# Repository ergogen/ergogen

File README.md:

# Ergogen

***Ergonomic Keyboard Generator***

<br>

The project aims to provide a common configuration format to describe ***ergonomic*** 2D layouts and generate automatic plates, cases, as well as un-routed PCBs for them. The project grew out of (and is an integral part of) the [Absolem keyboard], and shares its [Discord] server as well.

<div align = center>
<br>
<br>
<br>

---

[![Button WebUI]][WebUI]
[![Button Documentation]][Documentation]
[![Button Discord]][Discord]
[![Button Donate]][Donate]

---

</div>

<br>
<br>

## Getting Started

Until there's a proper "Getting started" guide, try getting acquainted with **Ergogen** by following these steps in order:

<br>

1. Read the **[Documentation]**.
    
    D'uuh.
    They're not complete by any measure, but should give you a fairly good idea what you're dealing with here.

    <br>
    
2. Try one of the web-based deployments.

    [![Button Official]][WebUI]   
    [![Button Unofficial]][Unofficial]
   
    (The difference being that Stable runs the latest official release, while Nightly offers early access to in-progress features, both for the Ergogen engine and the UI.)
    
    Load example configs, click things, rewrite things, look at outputs and see if things start to make sense.
   
    There is no need for you to download the **CLI** unless you want to do one of the following:
   
    - Preview in-development features
    - Use custom modifications
    - Contribute code
   
    <br>

3. Search the [`ergogen`][Topic] topic on GitHub.

    There, you can look at (and reverse engineer) a variety of real life configs using **Ergogen**.
    Pop them into the web UI to see what they do, tinker with them and things should start to make more sense.

    <br>

4. If a question persists after all of the above, feel free to ask it over on **[Discord]** and we'll do our best to help you out.

<br>

## Contributions

Feature ideas, documentation improvements, examples, tests, or pull requests welcome!
Get in touch on our **[Discord]**, and we can definitely find something you can help with, if you'd like to.

From an administrative standpoint, please note that we'd like to keep the Git history linear and the test suite comprehensive, so if you do issue a PR, make sure it's A) a straight chain of commits, B) it's always rebased on the current `develop`, and C) the test coverage remains at 100%.

<br>

## Sponsors

Huge thanks go to everyone who chooses to support my work!
But even huger thanks are due to the following, *distinguished* sponsors:

- [perce](https://madebyperce.com/)
- [Cache](https://github.com/MvEerd)
- [Neil Gilmour](https://github.com/neilgilmour)
- [ochief](https://github.com/ochief)
- [Alyx Brett](https://github.com/alyx-brett)

<!----------------------------------------------------------------------------->

[Absolem keyboard]: https://zealot.hu/absolem
[Documentation]: https://docs.ergogen.xyz
[Discord]: http://discord.ergogen.xyz
[WebUI]: https://ergogen.xyz
[Unofficial]: https://ergogen.ceoloide.com/
[Topic]: https://github.com/topics/ergogen
[Donate]: https://github.com/sponsors/mrzealot

<!--------------------------------{ Buttons }---------------------------------->

[Button WebUI]: https://img.shields.io/badge/Deployment-37a779?style=for-the-badge&logoColor=white&logo=AppleArcade
[Button Official]: https://img.shields.io/badge/Stable-37a779?style=for-the-badge
[Button Unofficial]: https://img.shields.io/badge/Nightly-yellow?style=for-the-badge
[Button Documentation]: https://img.shields.io/badge/Documentation-1793D1?style=for-the-badge&logoColor=white&logo=GitBook
[Button Discord]: https://img.shields.io/badge/Discord-5865F2?style=for-the-badge&logoColor=white&logo=Discord
[Button Donate]: https://img.shields.io/badge/Donate-EA4AAA?style=for-the-badge&logoColor=white&logo=githubsponsors

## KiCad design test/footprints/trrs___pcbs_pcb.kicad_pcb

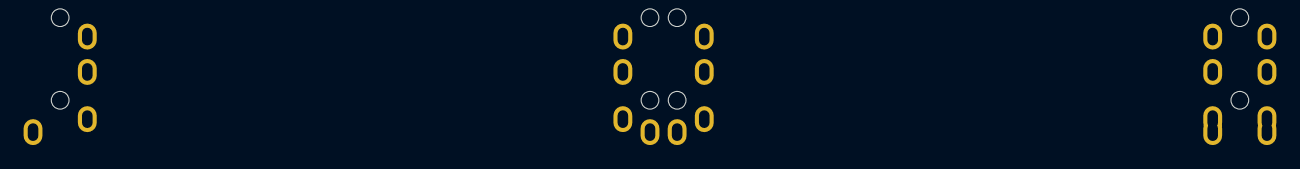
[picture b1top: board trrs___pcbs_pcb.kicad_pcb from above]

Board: 2 copper layers, 3 parts (0 on the bottom side), 4 nets, no tracks yet.

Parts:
TRRS1, TRRS2, TRRS3: TRRS-PJ-320A-dual

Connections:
A: TRRS1.1, TRRS2.1, TRRS3.1
B: TRRS1.2, TRRS2.2, TRRS3.2
C: TRRS1.3, TRRS2.3, TRRS3.3
D: TRRS1.4, TRRS2.4, TRRS3.4

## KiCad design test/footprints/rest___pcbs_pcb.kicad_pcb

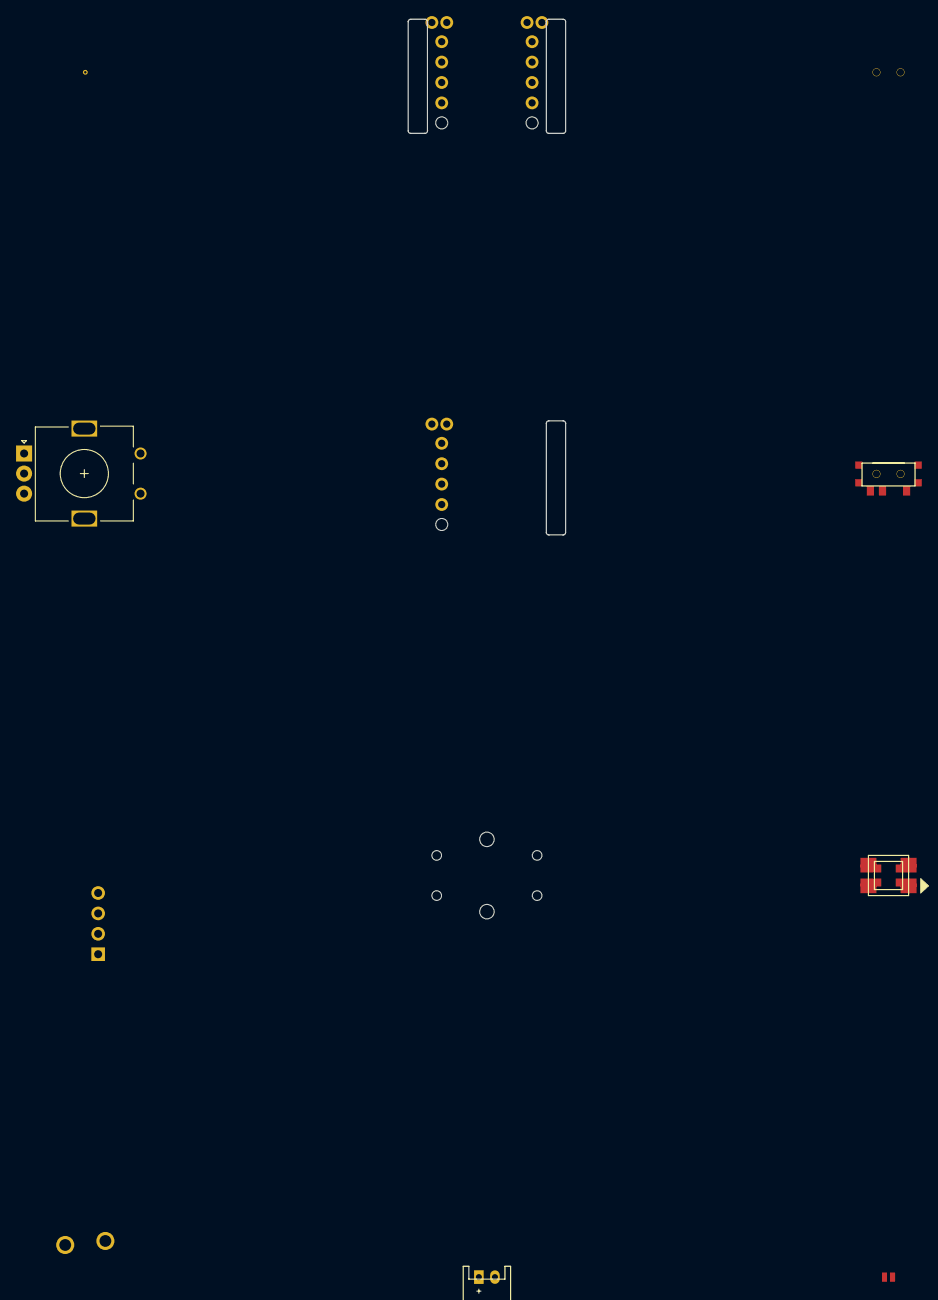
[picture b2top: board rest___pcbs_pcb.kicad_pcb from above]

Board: 2 copper layers, 9 parts (0 on the bottom side), 6 nets, no tracks yet.

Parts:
J1: Jumper
JST1: JST_PH_S2B-PH-K_02x2.00mm_Angled
LED1: WS2812B
OLED1: OLED; OLED_headers
ROT1: rotary_encoder
S1: ALPS
S2: OMRON_B3F-4055
T1, T2: SPDT_C128955

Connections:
GND: LED1.3, LED1.33, OLED1.1
VCC: LED1.1, LED1.11, OLED1.2
din: LED1.4, LED1.44
dout: LED1.2, LED1.22
from: J1.1, ROT1.1, S1.1, S2.1, S2.2, T1.1, T2.1
to: J1.2, ROT1.2, S1.2, S2.3, S2.4, T1.2, T2.2

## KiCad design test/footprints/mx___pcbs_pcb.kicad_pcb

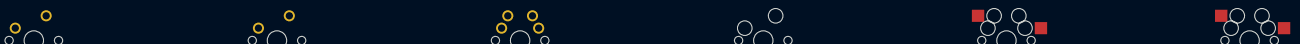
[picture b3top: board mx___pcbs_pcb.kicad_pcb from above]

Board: 2 copper layers, 6 parts (0 on the bottom side), 2 nets, no tracks yet.

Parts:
S1, S2, S3, S4, S5, S6: MX

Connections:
from: S1.1, S2.1, S3.1, S4.1, S5.1, S6.1
to: S1.2, S2.2, S3.2, S4.2, S5.2, S6.2

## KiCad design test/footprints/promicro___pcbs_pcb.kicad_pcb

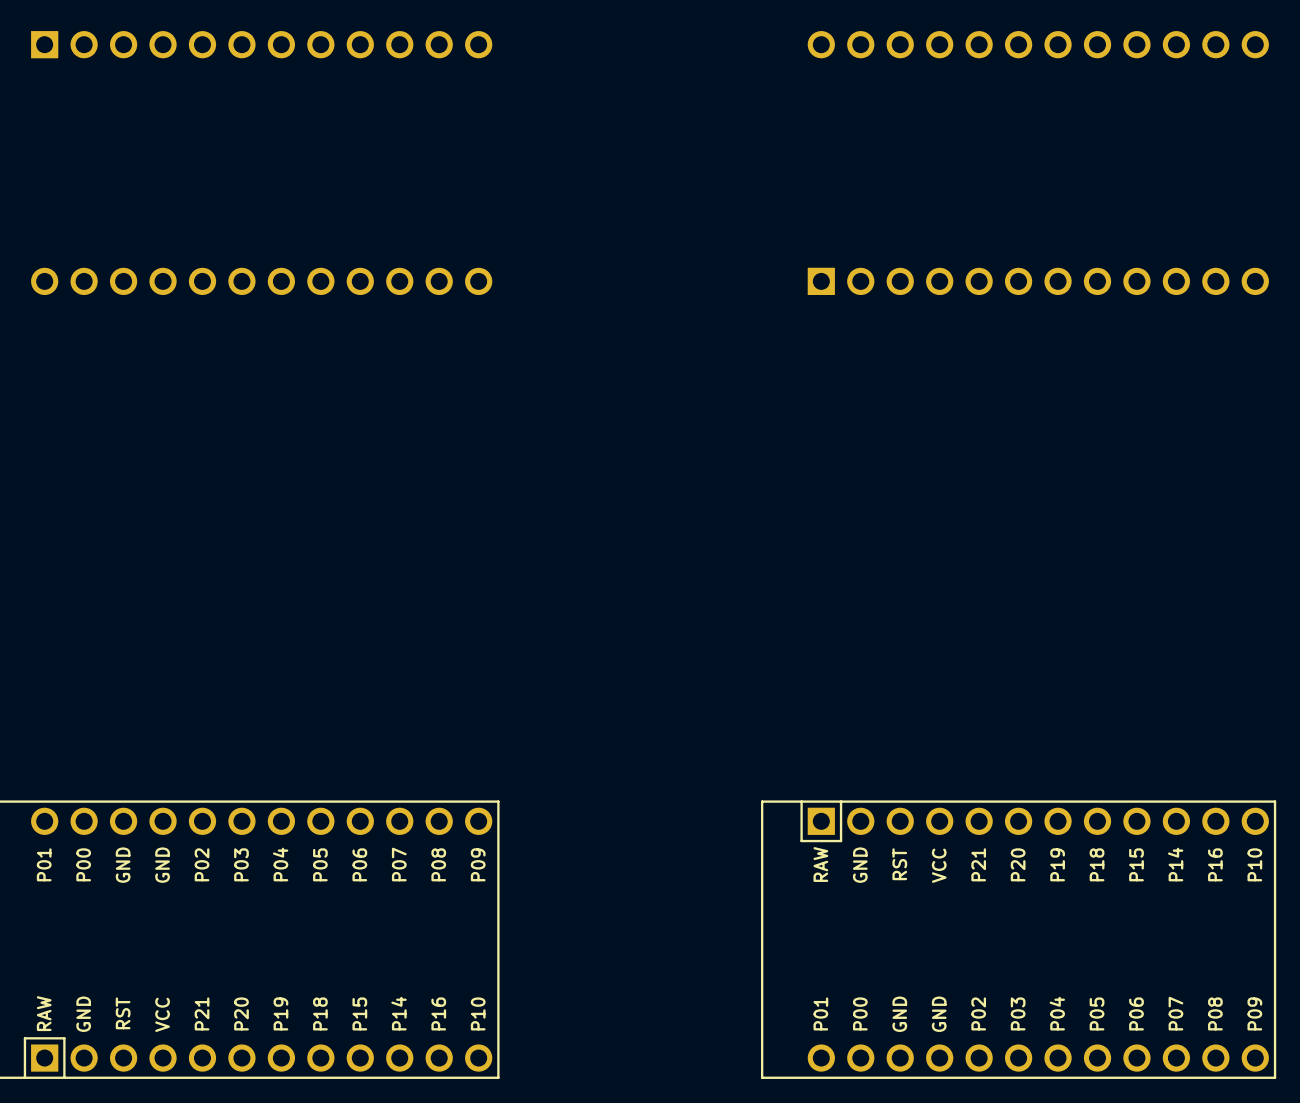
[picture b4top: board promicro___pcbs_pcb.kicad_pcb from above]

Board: 2 copper layers, 4 parts (0 on the bottom side), 22 nets, no tracks yet.

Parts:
MCU1, MCU2, MCU3, MCU4: ProMicro

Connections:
GND: MCU1.2, MCU1.15, MCU1.16, MCU2.2, MCU2.15, MCU2.16, MCU3.2, MCU3.15, MCU3.16, MCU4.2, MCU4.15, MCU4.16
P0: MCU1.14, MCU2.14, MCU3.14, MCU4.14
P1: MCU1.13, MCU2.13, MCU3.13, MCU4.13
P2: MCU1.17, MCU2.17, MCU3.17, MCU4.17
P3: MCU1.18, MCU2.18, MCU3.18, MCU4.18
P4: MCU1.19, MCU2.19, MCU3.19, MCU4.19
P5: MCU1.20, MCU2.20, MCU3.20, MCU4.20
P6: MCU1.21, MCU2.21, MCU3.21, MCU4.21
P7: MCU1.22, MCU2.22, MCU3.22, MCU4.22
P8: MCU1.23, MCU2.23, MCU3.23, MCU4.23
P9: MCU1.24, MCU2.24, MCU3.24, MCU4.24
P10: MCU1.12, MCU2.12, MCU3.12, MCU4.12
P14: MCU1.10, MCU2.10, MCU3.10, MCU4.10
P15: MCU1.9, MCU2.9, MCU3.9, MCU4.9
P16: MCU1.11, MCU2.11, MCU3.11, MCU4.11
P18: MCU1.8, MCU2.8, MCU3.8, MCU4.8
P19: MCU1.7, MCU2.7, MCU3.7, MCU4.7
P20: MCU1.6, MCU2.6, MCU3.6, MCU4.6
P21: MCU1.5, MCU2.5, MCU3.5, MCU4.5
RAW: MCU1.1, MCU2.1, MCU3.1, MCU4.1
RST: MCU1.3, MCU2.3, MCU3.3, MCU4.3
VCC: MCU1.4, MCU2.4, MCU3.4, MCU4.4

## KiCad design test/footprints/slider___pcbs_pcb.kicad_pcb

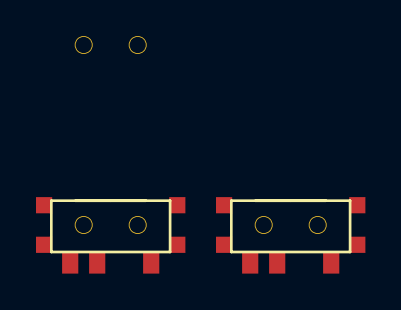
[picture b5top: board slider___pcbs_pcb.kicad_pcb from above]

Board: 2 copper layers, 3 parts (0 on the bottom side), 2 nets, no tracks yet.

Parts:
T1, T2, T3: SPDT_C128955

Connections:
A: T1.1, T3.1
COM: T1.2, T2.2, T3.2

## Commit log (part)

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2022-01-11 Outlines rewrite theoretically done
2022-01-12 (fix) allow mirroring around origin
2022-01-15 Filter implementation started
2022-01-15 Outlines rewrite, part 2
2022-01-15 Add filter tests
2022-01-16 Outlines rewrite actually done
2022-01-18 Roadmap update
2022-01-20 Bump patch version
2022-01-22 Support string templating for key-level attributes
2022-01-23 Fix rollup build warning
2022-01-23 More flexible semver handling
2022-01-24 Improve readme
2022-02-27 Support orient/rotate towards other points
2022-02-27 Make reference dumping easier during testing
2022-02-27 Changelog started
2022-03-26 Bump minimist from 1.2.5 to 1.2.6
    Bumps [minimist](https://github.com/substack/minimist) from 1.2.5 to 1.2.6.
    - [Release notes](https://github.com/substack/minimist/releases)
    - [Commits](https://github.com/substack/minimist/compare/1.2.5...1.2.6)
    ---
    updated-dependencies:
    - dependency-name: minimist
2022-03-26 fix: Remove superfluous rotation of 180 on a rectangular pad
2022-04-12 Update ergogami.yaml
    Clear and orginize
2022-04-12 Update ergogami.yaml
    wiring route fix
2022-04-12 Update ergogami.yaml
    fix wiring
2022-04-16 3D de-standalone-ification
2022-04-16 Outline scaling
2022-05-02 TRRS: properly showing p.ref instead of 'REF**'
2022-05-09 udpate promicro pretty
2022-05-09 samples
2022-05-17 Rename ergogami_alpha.yaml to Ergogami/ergogami_alpha.yaml
2022-05-18 More consistent formatting for promicro footprint + tests
2022-05-22 fixes
2022-05-22 ergogami v2 init
2022-05-22 update ergogami v2 alpha
2022-05-29 Outlining improvements
2022-05-31 Adjusted README Name
2022-05-31 Added License Badge
2022-05-31 Moved Getting Started Into Dedicated File
2022-05-31 Added Quicklinks
2022-05-31 Formatted Description + Added Showcase
2022-05-31 Adjusted Spacing
2022-08-08 Prevent duplicate net names between the main board and its mirror
2022-08-25 connects pads and THT terminals for less routing
2022-11-09 FULL
2022-11-14 Footprint sideloading tests
2022-11-22 Filtering applied to PCBs as well
2022-12-03 Generalize `asym` usage
2022-12-03 Minor comment fixes
2022-12-03 Improve PCB test readability
2022-12-03 Fix diode THT pad order
2022-12-04 Make outline/pcb anchor adjustments more generic
2022-12-04 Extend footprint test coverage
2022-12-04 Footprint parameter flattening, round 1
2022-12-04 Per-footprint mirror overrides, better coordinate support
2022-12-18 Missing const for web deployment
2022-12-18 Link updates
2023-01-08 Bump json5 from 2.2.1 to 2.2.3
    Bumps [json5](https://github.com/json5/json5) from 2.2.1 to 2.2.3.
    - [Release notes](https://github.com/json5/json5/releases)
    - [Changelog](https://github.com/json5/json5/blob/main/CHANGELOG.md)
    - [Commits](https://github.com/json5/json5/compare/v2.2.1...v2.2.3)
    ---
    updated-dependencies:
2023-01-11 fix: typo in error message if using incorrect type for stagger
2023-01-14 ignore line endings in cli tests
2023-01-14 expand code coverage for `choc` footprint
2023-01-14 expand code coverage for `mx` footprint
2023-01-14 expand code coverage for `pad` footprint
2023-01-14 expand code coverage for `anchor.js`
2023-01-14 New Kicad format plus tests
2023-01-14 expand code coverage for `filter.js`
2023-01-14 fix: use all but last character as `expand` value in `expand_shorthand`
2023-01-15 expand code coverage for `pcbs.js`
2023-01-15 expand code coverage for `kle.js`
2023-01-16 Add parenthesis to title block
2023-01-23 Bugfix for `expand_shorthand` (#79)
2023-01-23 Improve readme formatting (#62)
    * Fixed LICENSE File Name
    * Adjusted README Name
    * Formatted Contribution Section
    * Added License Badge
    * Formatted Getting Started
    * Moved Getting Started Into Dedicated File
2023-01-23 Fix multiple extrusions of the same outline in cases
2023-01-23 Readme postprocessing
2023-01-23 test: code coverage for `expand_shorthand`
2023-01-23 Add array to footprint param types (#76)
2023-01-23 Getting coverage to 100%
2023-01-31 fix: handle backslashes in windows tests
2023-02-09 Filter/mirror bugfix
2023-03-17 Templating bugfix (#86)
2023-03-17 4.0.1
2023-03-17 v4.0.1 release as WebUI 1.4.1
2023-03-18 Filter negation bugfix
2023-03-18 v4.0.2 release as WebUI 1.4.2
2023-03-29 Add extra note on "read documentation" about v4
2023-04-19 Add pro micro pretty footprint
2023-04-19 create fourne w correct footprints
2023-05-01 Add donate button to readme
2023-05-08 Sponsor fixes
2023-05-20 Independent per-point adjustment
2023-05-20 4.0.4
2023-05-20 v4.0.4 release as WebUI 1.4.3
2023-05-31 Allow outline adjusts to use shape-specific units
2023-06-17 add outline to niceview
2023-07-15 Added intersect aggregator
2023-07-17 Addressed stylistic PR feedback
2023-07-17 Revert "Set the rotation of the intersected point to the second point’s rotation"
    This reverts commit d210a98f79a8866519fc9695487a9ea235167b8b.
2023-07-18 Add assert to check for exactly 2 parts
2023-07-19 Change the assert string to use ${name.length}
2023-07-19 Update intersect logic to consider negative Y axis
2023-07-19 Add intersect aggregator (#102)
    * Added intersect aggregator
    * Addressed stylistic PR feedback
    * Set the rotation of the intersected point to the second point’s rotation
    * Revert "Set the rotation of the intersected point to the second point’s rotation"
    This reverts commit d210a98f79a8866519fc9695487a9ea235167b8b.
    * Adjusted aggregate function to not need axis1 and axis2 parameters
2023-08-13 feat: add parametric breakout board
2023-08-24 Add point as a parameter to footprints
2023-09-09 add 'global_net' to params structure for access (read and read/write) to global nets in footprints
2023-09-18 Adding option for circle radius to be an anchor.
    Rather than just accepting a number, the circle outline can now also
    accept an anchor. When an anchor is given, the radius is calculated as
    the distance from the origin of the circle(s) to the anchor point.
2023-09-18 Adding midpoint aggregator.
    The midpoint aggregator takes 3 points and finds a "midpoint" that is
    equidistant to all the given points.
2023-12-25 Inject outlines from SVGs in bundle
2023-12-25 Add jsdom dependency (oops)
2023-12-25 Fix tests and add coverage for injected outlines
2023-12-28 Change test references from src/ to build/ and update more configs
2023-12-28 Convert point.js to point.ts
2024-01-01 Add type declarations for node dependencies
2024-01-01 add trackball footprint file
2024-01-01 get rotation right
2024-01-04 Allows more than one via
    The .kicad_pcb file seems to be invalid if you have two vias with a REF** reference
    This change puts in a dynamic reference and defaults the designator to V
2024-01-22 Package audit
2024-01-23 Injectable PCB templates
2024-03-29 Outsource kicad outline conversion to pcb templates
2024-04-09 KiCad8 PCB template
2024-04-09 Template dependency injection
2024-04-14 Prevent circular dependencies in $extends
2024-05-12 when --clean enabled instead of deleting output dir just clean up its content
2025-08-23 Remove `bezier` outline code
2025-11-01 MakerJS dependency reset and tests
2025-11-01 Add skeleton for closed Bezier splines
2025-11-01 Fix variable declaration
2025-11-01 Add check for number of points based on type, and default to `quadratic` type
2025-11-01 Fix wrong variable declaration
2025-11-01 Add bezier utility function
2025-11-01 Remove wrong `bezier` package dependency
2025-11-01 Add `hull` type to outlines
2025-11-01 Fix bounding box logic and BezierCurve creation
2025-11-01 Remove require for Bezier
2025-11-01 Add intermediate points
2025-11-01 Add rotation test case
2025-11-01 Switch from `let` to `const` since variables are not modified
2025-11-01 Add parameter / syntax validation
2025-11-01 Fix rollup.config.mjs (use Node 20+ import syntax)
2025-11-01 Change the path segment logic so that the starting point is taken from the previous segment
2025-11-01 Fix: Resolve variables in mirror properties
    Previously, when a variable was used for a property inside a `mirror`
    configuration (e.g., `width: my_var`), it was not resolved correctly.
    This was because the sanitization and variable resolution process was
    not re-applied after the mirrored point's metadata was extended with
    the mirror configuration.
    This commit fixes the issue by passing the `units` object to the
2025-11-01 `--clean` now cleans the output dir instead of deleting it
    The most common behavior for a CLI `--clean` flag is to delete just the contents of the artifact / output folder, not the folder itself.
    This ensures that the folder (and especially any required permissions or configuration) remains in place for subsequent runs, avoiding issues where the folder needs to be recreated.
    Deleting only the contents is safer and more user-friendly, especially if other processes or scripts expect the folder to exist.
    This commit closes https://github.com/ergogen/ergogen/pull/131
2025-11-01 Address `npm audit` vulnerabilities with `npm audit fix`
2025-11-01 Update npm packages to their latest version
    Additionally, changed `yaml.safeLoad` to `yaml.load` as this is now safe by default in js-yaml 4.
    This commit closes https://github.com/ergogen/ergogen/pull/149
2025-11-01 Add `height` to the `mirror_variable` test (issue #145)
    Test coverage highlighted that only `width` but not `height` was explicitly being tested. Slightly amended the test to add `height` as well, to reach 100% test coverage.
2025-11-01 Add test cases for `path`
    Test cases cover both cases when one of the segment types is used first, meaning it defines all points, or when it's defined `[2nd...N-th]` in the path, meaning the first point is inherited from the 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
2025-11-01 Remove redundant `operation: stack` entries from path outlines
2025-11-01 fix(test): use portable command for checking file permissions
2025-11-01 Implement date mocking, to ensure `kicad8` tests are deterministic
    The `kicad8.js` template generates `*.kicad_pcb` outputs that contain a dynamic date, based on global `Date` object. This makes tests fail since they compare to a fixed output reference, with an stat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
2025-11-01 Add additional `line` segment to path definition to reach 100% coverage for `outlines.js`
2025-11-01 Remove unused `bezier` code, and fix `s_curve` switch case
2025-11-01 refactor(clean): remove `clean` CLI test command and related output files
    The command used is tied too much to *nix environments and doesn't work fully across different OS.
    While coverage remains at 100%, a different test will be created for the `--clean` argument
2025-11-02 Support for newer OpenJSCAD
2025-11-02 Update README to remove comment about official GUI
2025-11-02 4.2.1
2025-11-09 Update generator version to 4.2.1 in KiCad PCB template
2025-11-09 Add clockwise and counter-clockwise options to hull configuration and update related DXF files
2026-01-28 Add 'maxArcFacet' meta field to fix issue where all circles & arcs have exactly 32 segments
2026-05-12 Add CadQuery case Python exporter
2026-05-13 Add cases-only CLI output option
2026-06-20 Update generator version to 4.2.1 (#12)
2026-06-20 Revert "Add clockwise and counter-clockwise options to hull configuration and update related DXF files"
    This reverts commit 67740334c42379c82eea914a17ddca88e7826e21.
2026-06-20 Enhance inheritance tests
    Enhance inheritance tests to cover non-object/non-array types: string, boolean, and number and achieve 100% test coverage on `src/prepare.js`
2026-06-20 Implement $concat preprocessing support (#13)
    # $concat Preprocessing Support
    ## Overview
    This change introduces a new preprocessing function, `$concat(...)`, which allows users to concatenate strings in their Ergogen YAML configurations. This is particularly useful for dynamically genera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
    ## Syntax
    The syntax for `$concat` is as follows:
    `$concat(arg1, arg2, ..., argN)`
2026-06-21 Bump makerjs from 0.18.2 to 0.19.1
2026-06-21 Bump makerjs from 0.19.1 to 0.19.2
2026-06-21 Bump rollup from 4.52.4 to 4.62.2
2026-06-21 Bump rollup/plugin-commonjs from 28.0.7 to 29.0.3
2026-06-21 Bump nyc from 17.1.0 to 18.0.0
2026-06-21 Bump glob from 11.0.3 to 13.0.6
